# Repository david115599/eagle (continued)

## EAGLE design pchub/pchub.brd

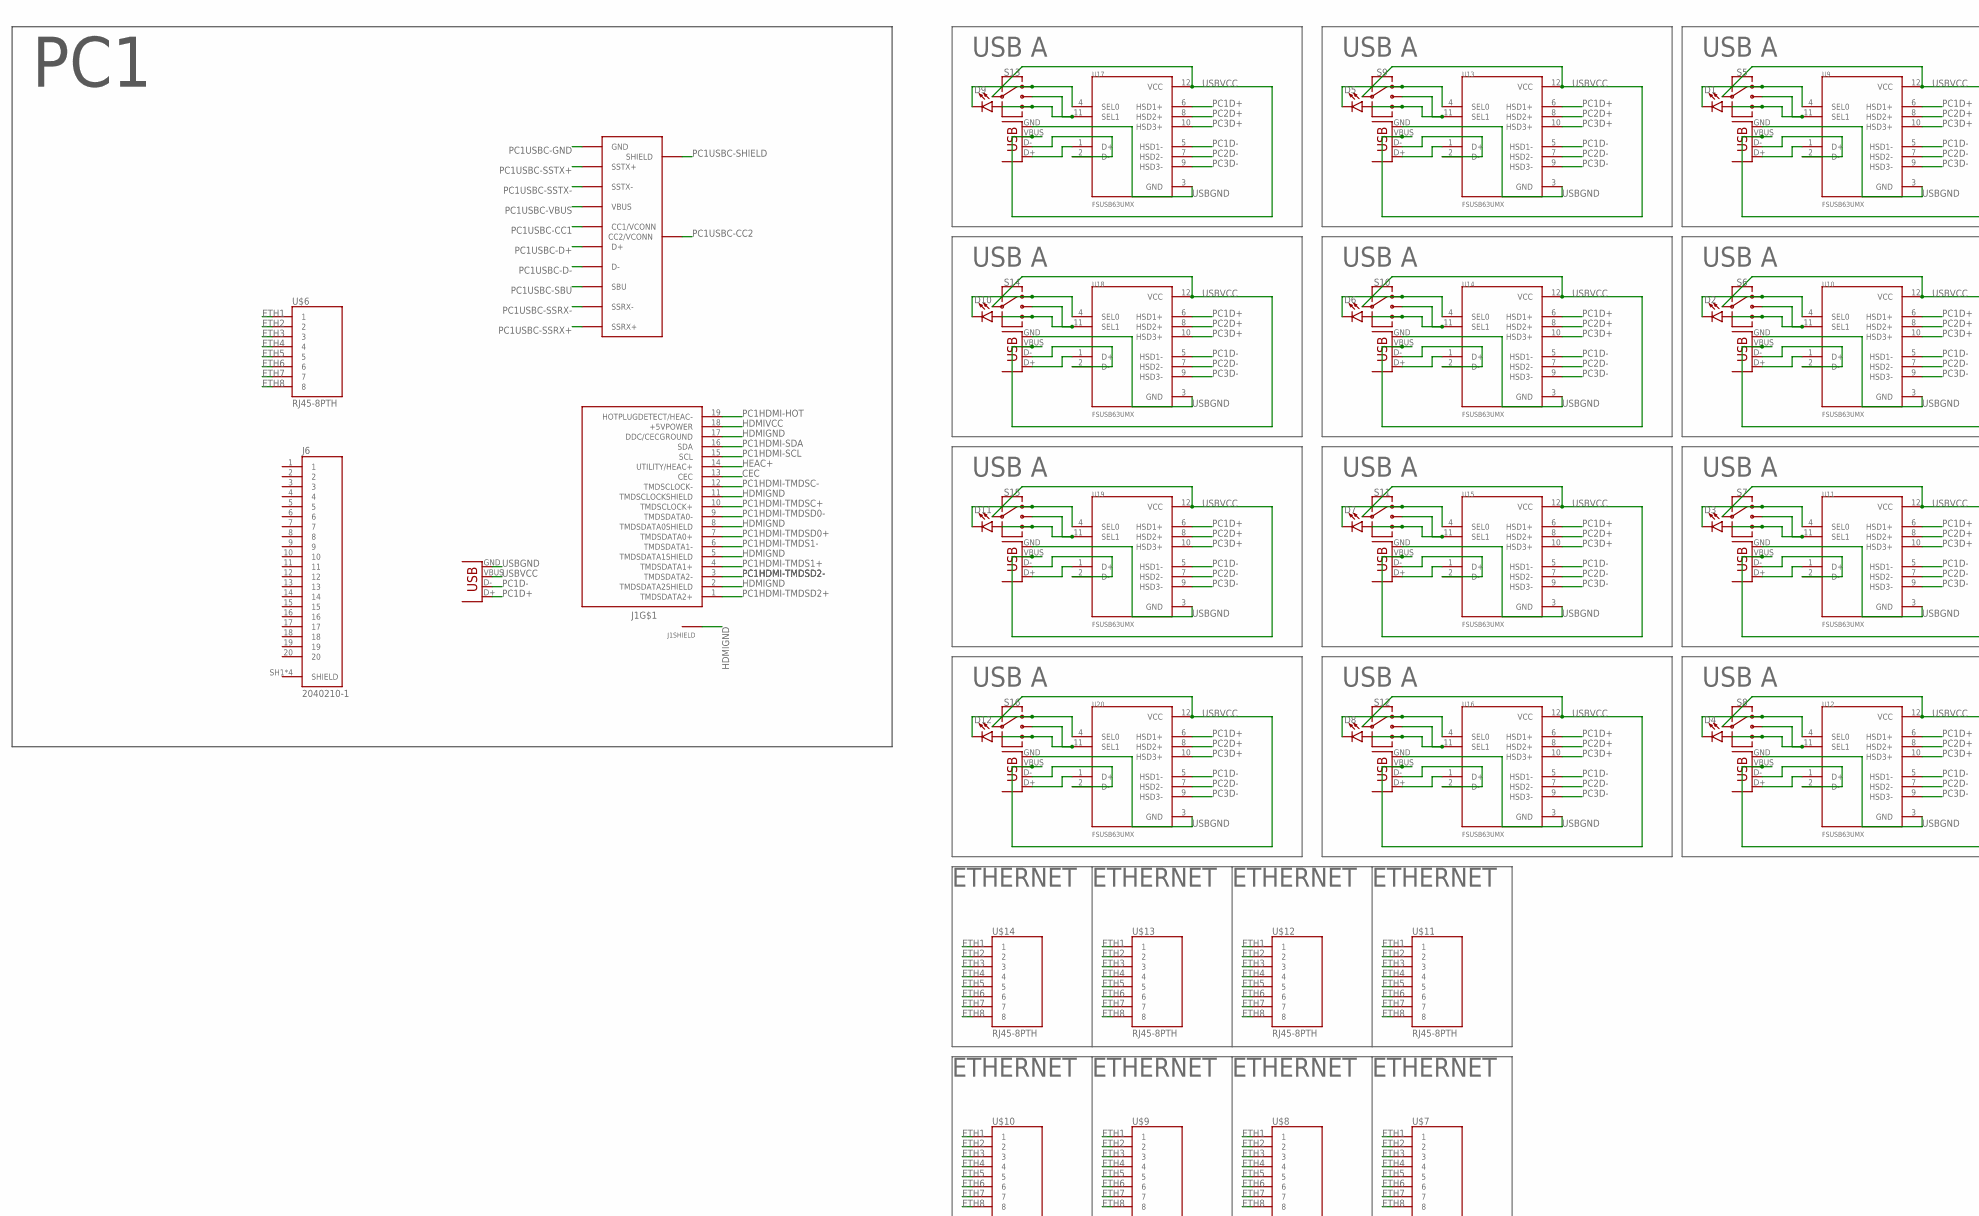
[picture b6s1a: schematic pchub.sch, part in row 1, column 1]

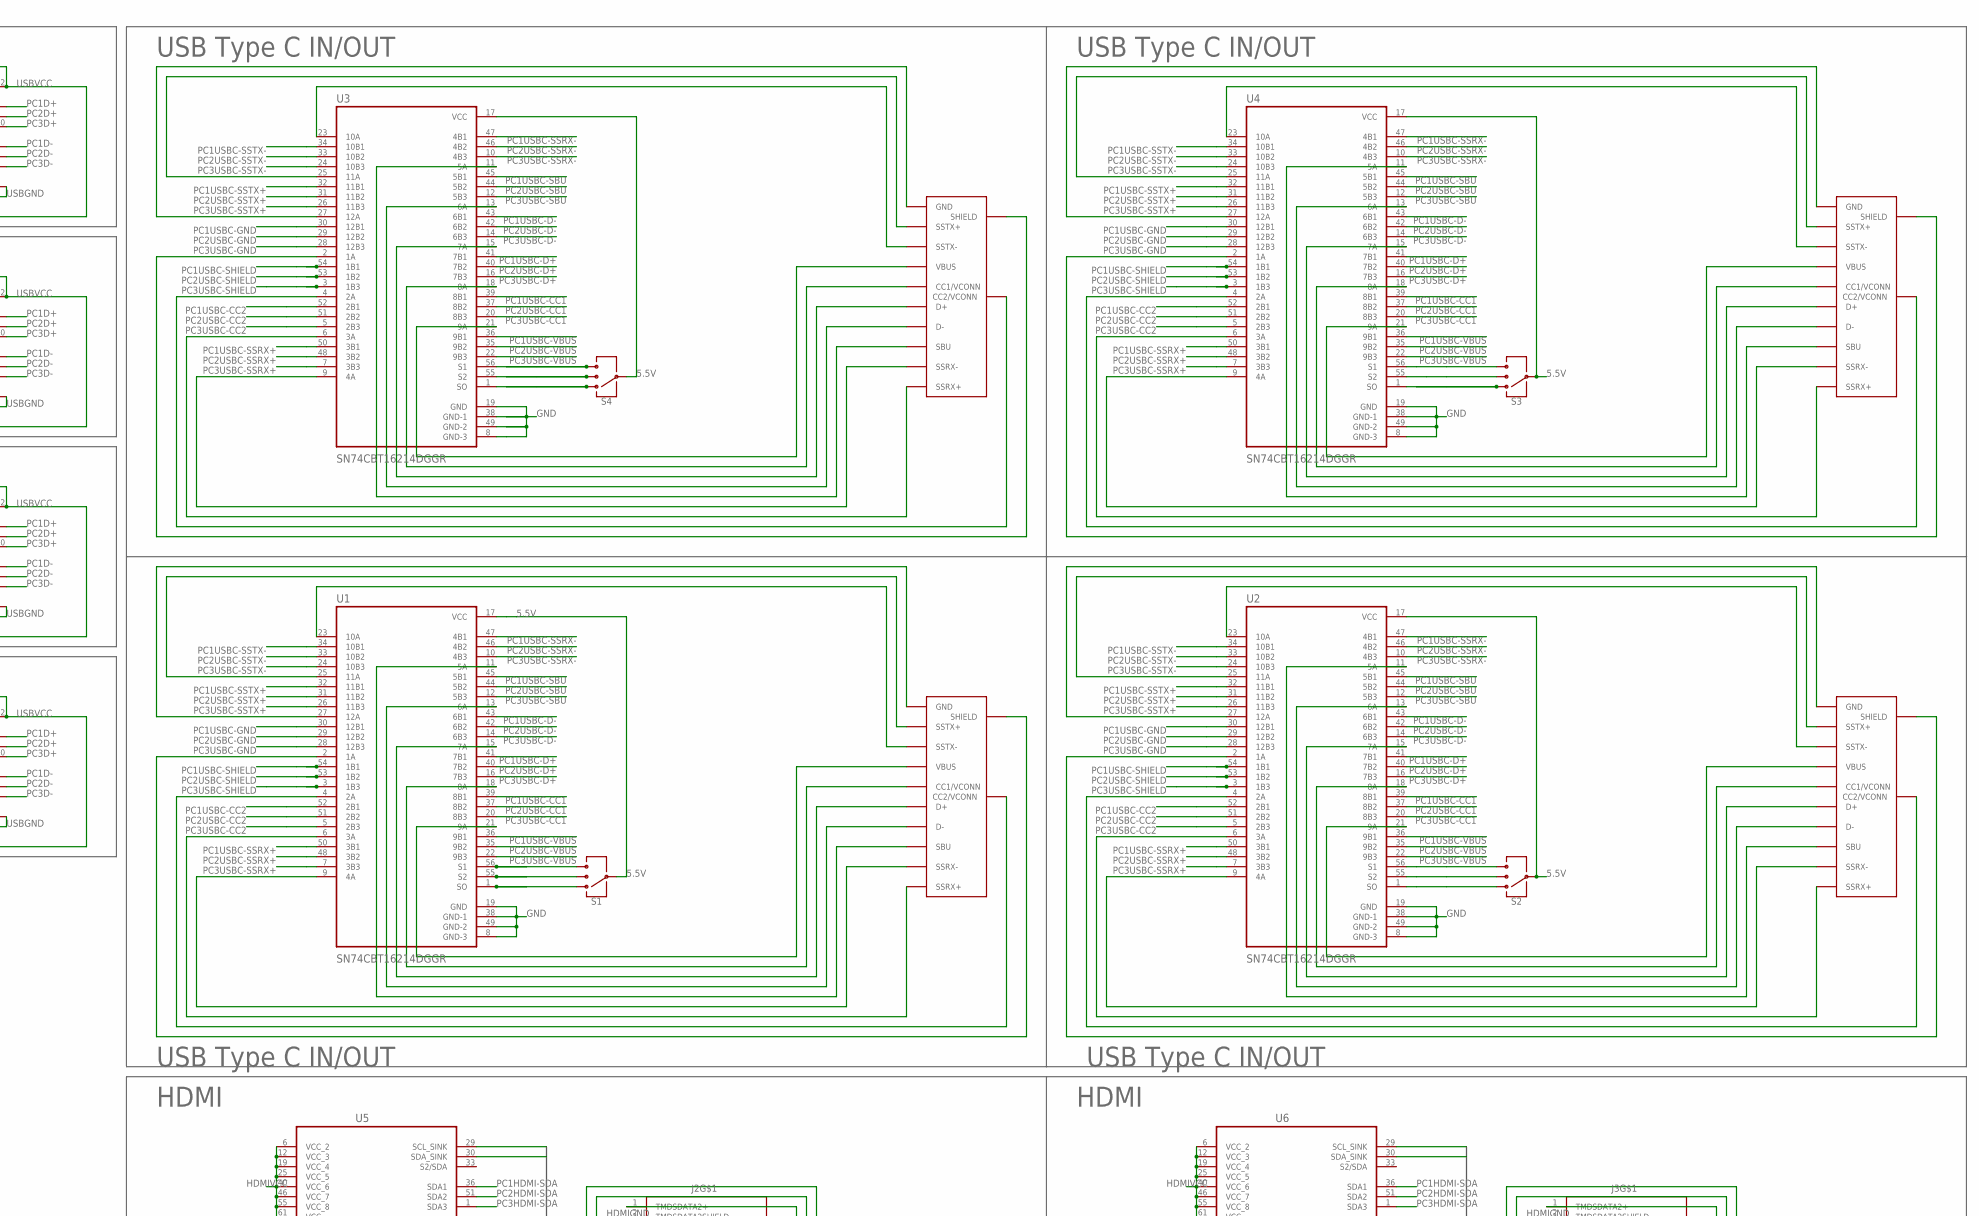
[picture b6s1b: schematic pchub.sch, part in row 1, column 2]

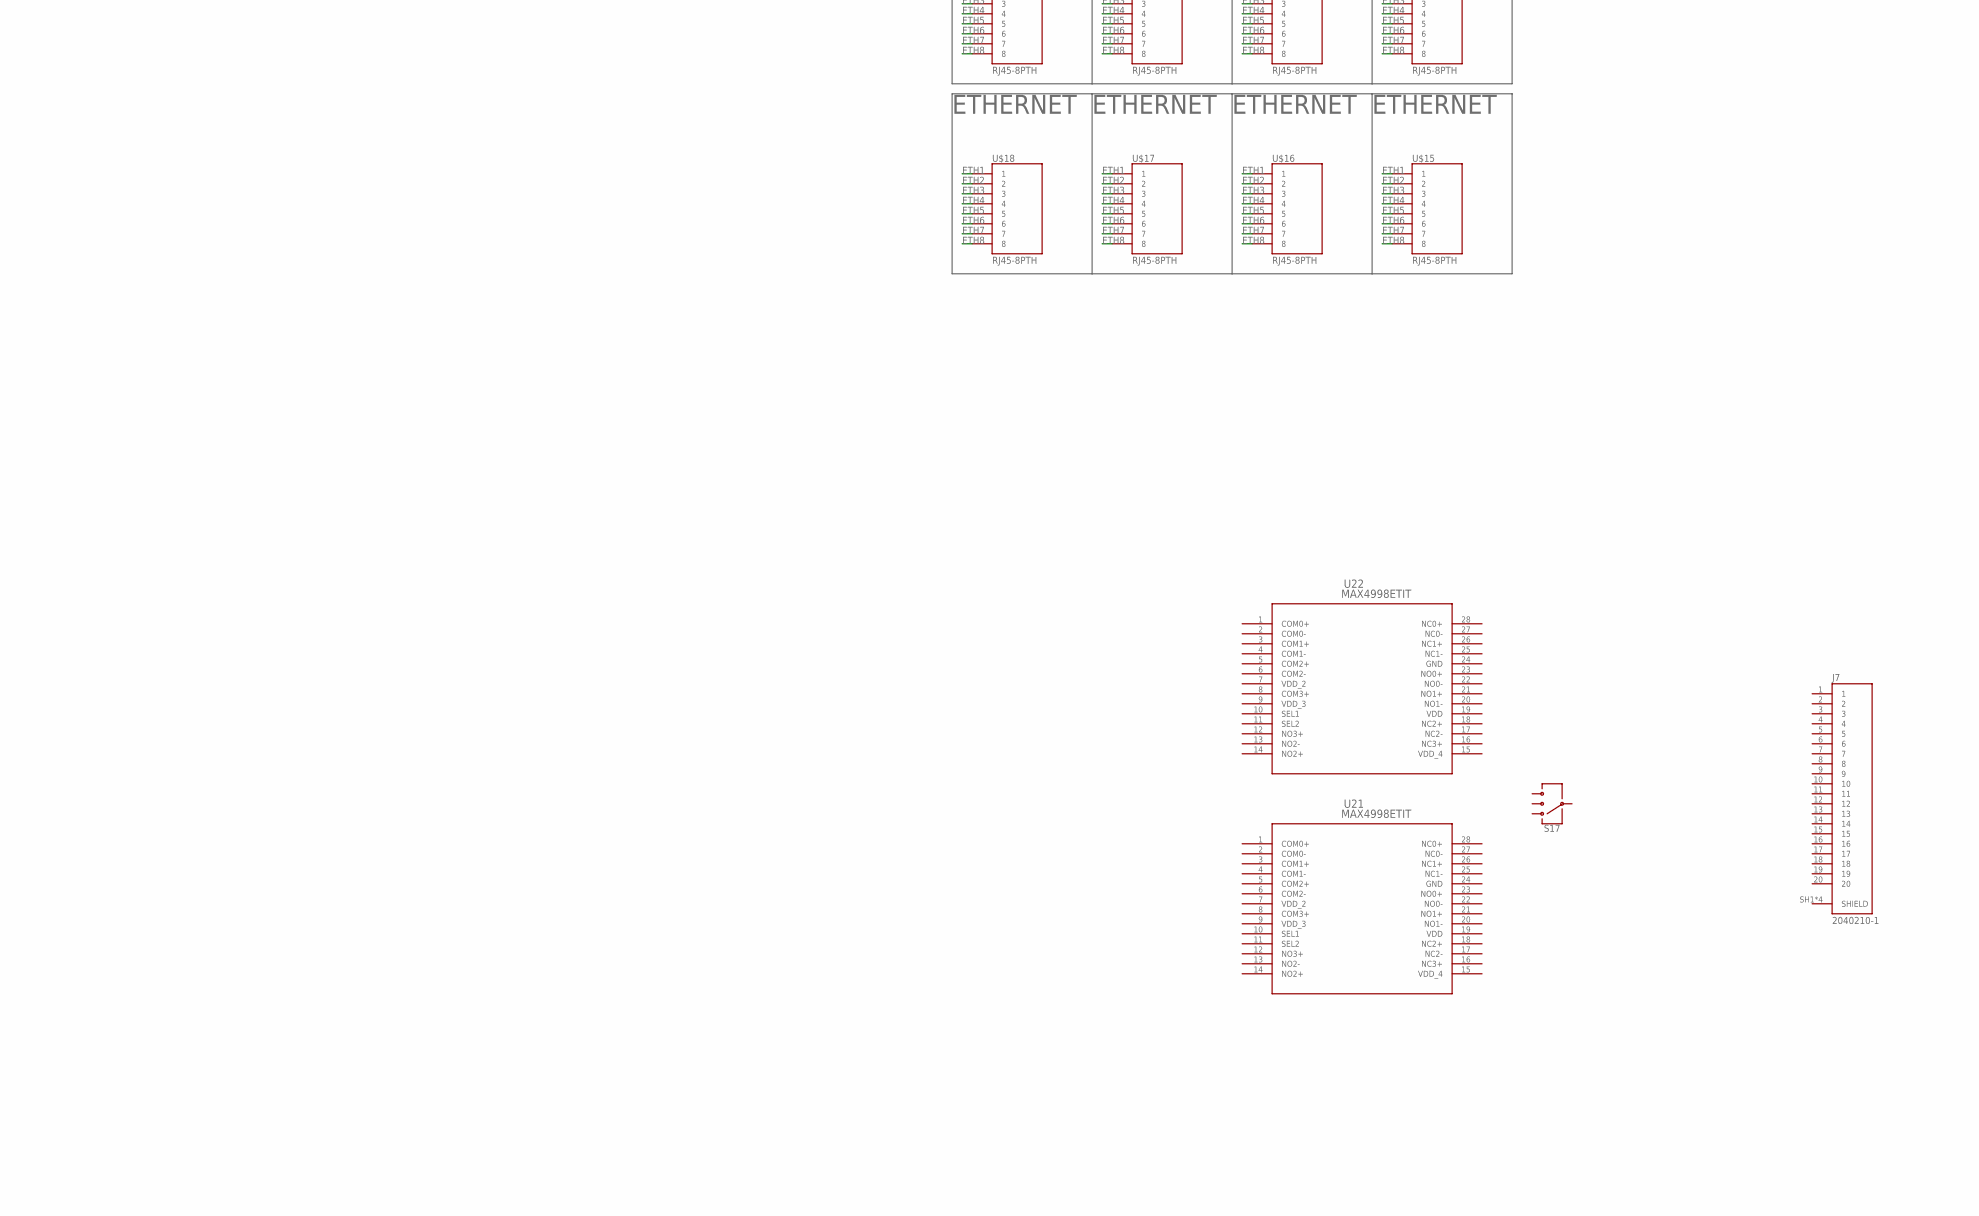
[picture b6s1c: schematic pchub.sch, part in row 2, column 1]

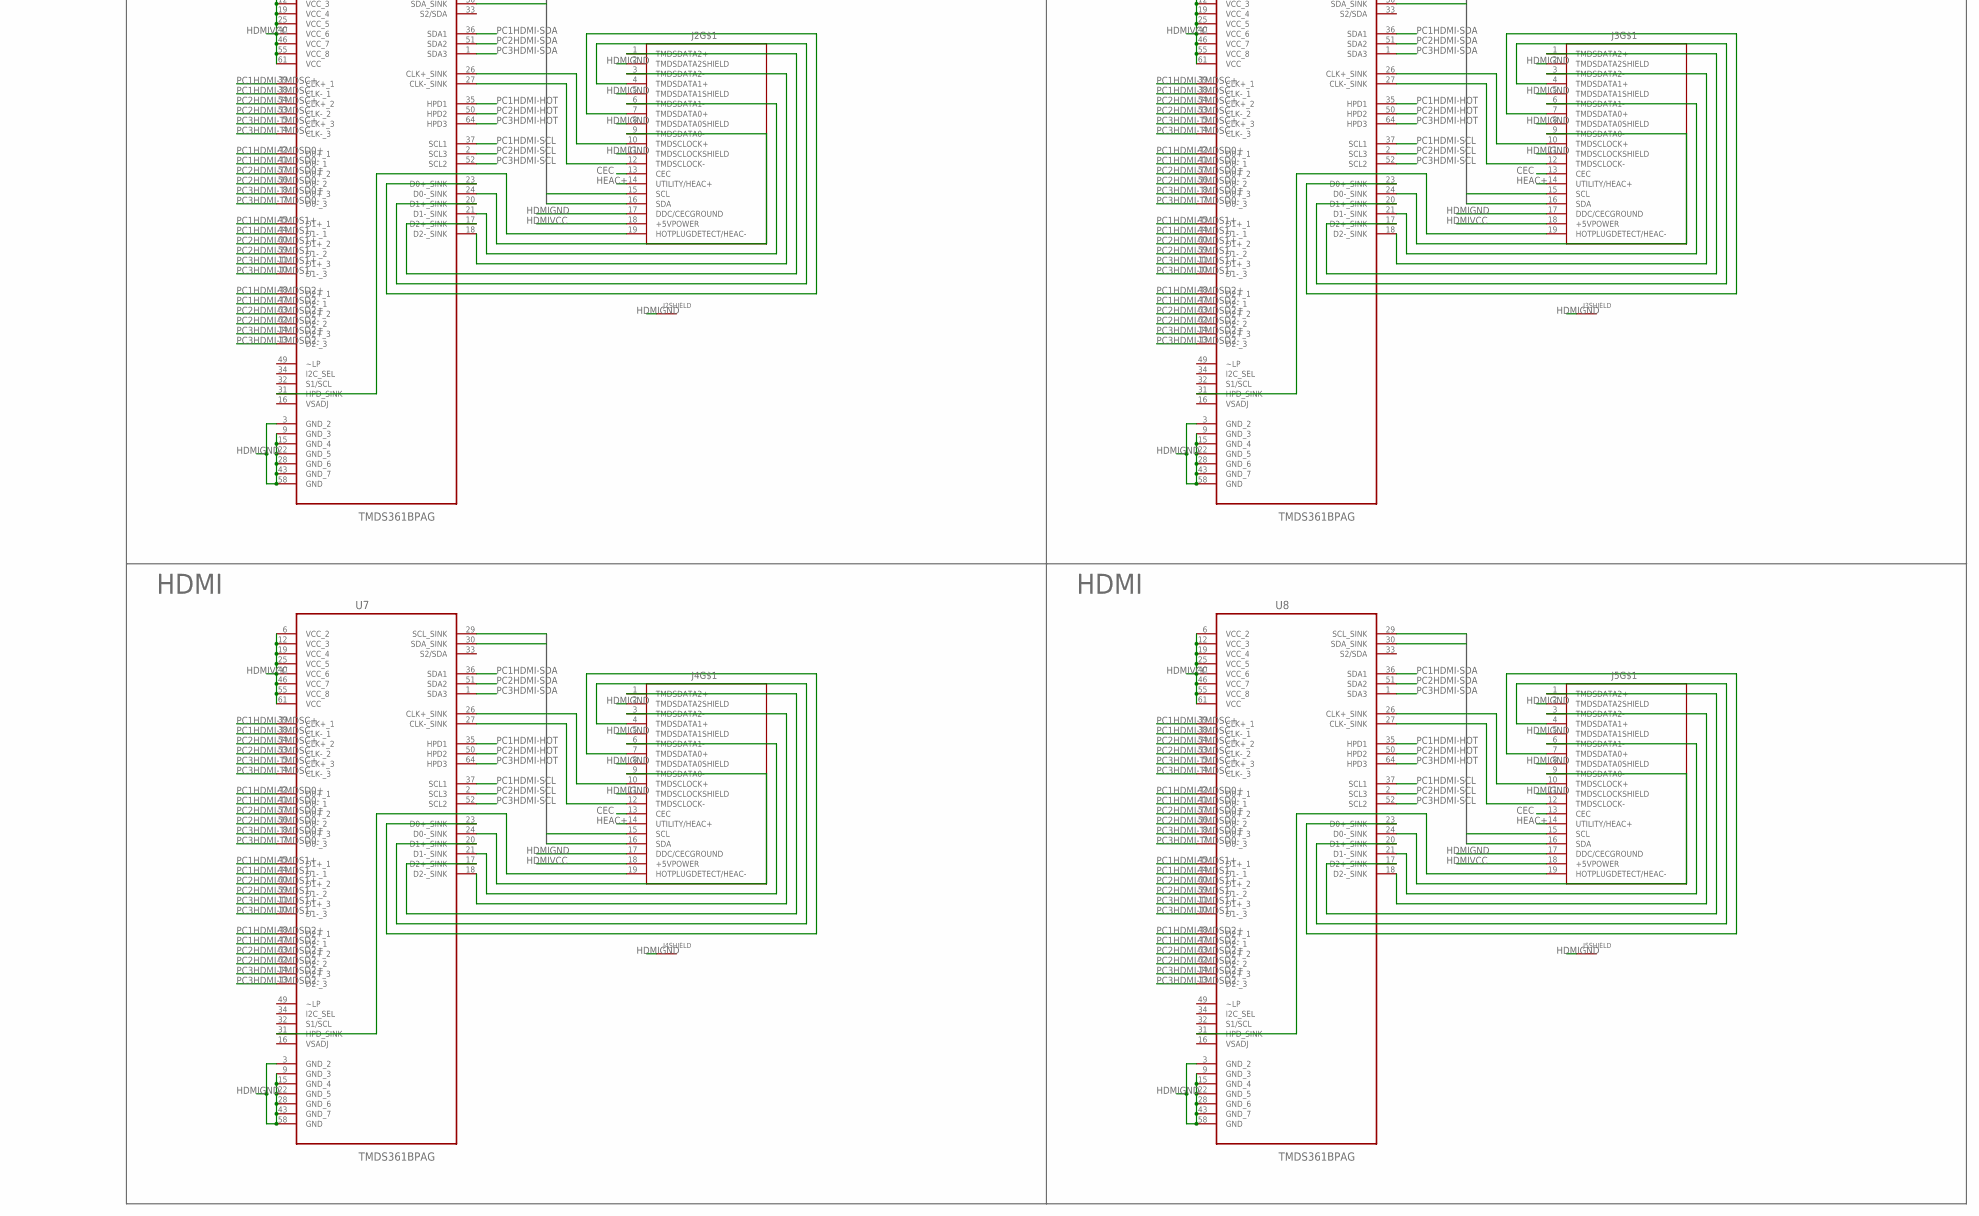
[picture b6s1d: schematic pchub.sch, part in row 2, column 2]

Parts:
D1, D2, D3, D4, D5, D6, D7, D8, D9, D10, D11, D12: LED-FKIT-1206; FKIT-LED-1206
J1, J2, J3, J4, J5: 685119134923
J6, J7: 2040210-1; TE_2040210-1
S1, S2, S3, S4, S5, S6, S7, S8, S9, S10, S11, S12, S13, S14, S15, S16, S17: SWITCH-SP3T-SMD; SWITCH_SP3T_SMD
U1, U2, U3, U4: SN74CBT16214DGGR; SOP50P810X120-56N
U5, U6, U7, U8: TMDS361BPAG; QFP50P1200X1200X120-64N
U9, U10, U11, U12, U13, U14, U15, U16, U17, U18, U19, U20: FSUSB63UMX; QFN40P180X180X55-12N
U21, U22: MAX4998ETIT; 21-0184D
U$1, U$2, U$3, U$4, U$5: USB-TYPE-C; USB-TYPE-C-SMT
U$6, U$7, U$8, U$9, U$10, U$11, U$12, U$13, U$14, U$15, U$16, U$17, U$18: RJ45-8PTH; RJ45-8
X1, X2, X3, X4, X5, X6, X7, X8, X9, X10, X11, X12, X13: USB; USB-A-S-NOSILK-FEMALE

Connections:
5.5V: S1.3, S2.3, S3.3, S4.3, U1.17 (VCC), U2.17 (VCC), U3.17 (VCC), U4.17 (VCC)
CEC: J1.13 (CEC), J2.13 (CEC), J3.13 (CEC), J4.13 (CEC), J5.13 (CEC)
ETH1: U$6.1, U$7.1, U$8.1, U$9.1, U$10.1, U$11.1, U$12.1, U$13.1, U$14.1, U$15.1, U$16.1, U$17.1, U$18.1
ETH2: U$6.2, U$7.2, U$8.2, U$9.2, U$10.2, U$11.2, U$12.2, U$13.2, U$14.2, U$15.2, U$16.2, U$17.2, U$18.2
ETH3: U$6.3, U$7.3, U$8.3, U$9.3, U$10.3, U$11.3, U$12.3, U$13.3, U$14.3, U$15.3, U$16.3, U$17.3, U$18.3
ETH4: U$6.4, U$7.4, U$8.4, U$9.4, U$10.4, U$11.4, U$12.4, U$13.4, U$14.4, U$15.4, U$16.4, U$17.4, U$18.4
ETH5: U$6.5, U$7.5, U$8.5, U$9.5, U$10.5, U$11.5, U$12.5, U$13.5, U$14.5, U$15.5, U$16.5, U$17.5, U$18.5
ETH6: U$6.6, U$7.6, U$8.6, U$9.6, U$10.6, U$11.6, U$12.6, U$13.6, U$14.6, U$15.6, U$16.6, U$17.6, U$18.6
ETH7: U$6.7, U$7.7, U$8.7, U$9.7, U$10.7, U$11.7, U$12.7, U$13.7, U$14.7, U$15.7, U$16.7, U$17.7, U$18.7
ETH8: U$6.8, U$7.8, U$8.8, U$9.8, U$10.8, U$11.8, U$12.8, U$13.8, U$14.8, U$15.8, U$16.8, U$17.8, U$18.8
GND: U1.8 (GND-3), U1.19 (GND), U1.38 (GND-1), U1.49 (GND-2), U2.8 (GND-3), U2.19 (GND), U2.38 (GND-1), U2.49 (GND-2), U3.8 (GND-3), U3.19 (GND), U3.38 (GND-1), U3.49 (GND-2), U4.8 (GND-3), U4.19 (GND), U4.38 (GND-1), U4.49 (GND-2), U21.24 (GND), U22.24 (GND)
HDMIGND: J1.2 (TMDSDATA2SHIELD), J1.5 (TMDSDATA1SHIELD), J1.8 (TMDSDATA0SHIELD), J1.11 (TMDSCLOCKSHIELD), J1.17 (DDC/CECGROUND), J1.SHELL (SHIELD), J1.SHELL1 (SHIELD), J1.SHELL2 (SHIELD), J1.SHELL3 (SHIELD), J2.2 (TMDSDATA2SHIELD), J2.5 (TMDSDATA1SHIELD), J2.8 (TMDSDATA0SHIELD), J2.11 (TMDSCLOCKSHIELD), J2.17 (DDC/CECGROUND), J2.SHELL (SHIELD), J2.SHELL1 (SHIELD), J2.SHELL2 (SHIELD), J2.SHELL3 (SHIELD), J3.2 (TMDSDATA2SHIELD), J3.5 (TMDSDATA1SHIELD), J3.8 (TMDSDATA0SHIELD), J3.11 (TMDSCLOCKSHIELD), J3.17 (DDC/CECGROUND), J3.SHELL (SHIELD), J3.SHELL1 (SHIELD), J3.SHELL2 (SHIELD), J3.SHELL3 (SHIELD), J4.2 (TMDSDATA2SHIELD), J4.5 (TMDSDATA1SHIELD), J4.8 (TMDSDATA0SHIELD), J4.11 (TMDSCLOCKSHIELD), J4.17 (DDC/CECGROUND), J4.SHELL (SHIELD), J4.SHELL1 (SHIELD), J4.SHELL2 (SHIELD), J4.SHELL3 (SHIELD), J5.2 (TMDSDATA2SHIELD), J5.5 (TMDSDATA1SHIELD), J5.8 (TMDSDATA0SHIELD), J5.11 (TMDSCLOCKSHIELD), J5.17 (DDC/CECGROUND), J5.SHELL (SHIELD), J5.SHELL1 (SHIELD), J5.SHELL2 (SHIELD), J5.SHELL3 (SHIELD), U5.3 (GND_2), U5.9 (GND_3), U5.15 (GND_4), U5.22 (GND_5), U5.28 (GND_6), U5.43 (GND_7), U5.58 (GND), U6.3 (GND_2), U6.9 (GND_3), U6.15 (GND_4), U6.22 (GND_5), U6.28 (GND_6), U6.43 (GND_7), U6.58 (GND), U7.3 (GND_2), U7.9 (GND_3), U7.15 (GND_4), U7.22 (GND_5), U7.28 (GND_6), U7.43 (GND_7), U7.58 (GND), U8.3 (GND_2), U8.9 (GND_3), U8.15 (GND_4), U8.22 (GND_5), U8.28 (GND_6), U8.43 (GND_7), U8.58 (GND)
HDMIVCC: J1.18 (+5VPOWER), J2.18 (+5VPOWER), J3.18 (+5VPOWER), J4.18 (+5VPOWER), J5.18 (+5VPOWER), U5.6 (VCC_2), U5.12 (VCC_3), U5.19 (VCC_4), U5.25 (VCC_5), U5.40 (VCC_6), U5.46 (VCC_7), U5.55 (VCC_8), U5.61 (VCC), U6.6 (VCC_2), U6.12 (VCC_3), U6.19 (VCC_4), U6.25 (VCC_5), U6.40 (VCC_6), U6.46 (VCC_7), U6.55 (VCC_8), U6.61 (VCC), U7.6 (VCC_2), U7.12 (VCC_3), U7.19 (VCC_4), U7.25 (VCC_5), U7.40 (VCC_6), U7.46 (VCC_7), U7.55 (VCC_8), U7.61 (VCC), U8.6 (VCC_2), U8.12 (VCC_3), U8.19 (VCC_4), U8.25 (VCC_5), U8.40 (VCC_6), U8.46 (VCC_7), U8.55 (VCC_8), U8.61 (VCC)
HEAC+: J1.14 (UTILITY/HEAC+), J2.14 (UTILITY/HEAC+), J3.14 (UTILITY/HEAC+), J4.14 (UTILITY/HEAC+), J5.14 (UTILITY/HEAC+)
unnamed: U2.18 (8A), U$2.5 (CC1/VCONN)
unnamed: U2.23 (10A), U$2.3 (SSTX-), U$2.B3 (SSTX-)
unnamed: U2.25 (11A), U$2.2 (SSTX+), U$2.B2 (SSTX+)
unnamed: U2.27 (12A), U$2.1 (GND), U$2.12 (GND), U$2.B1 (GND), U$2.B12 (GND)
unnamed: U2.2 (1A), U$2.P$1 (SHIELD), U$2.P$2 (SHIELD), U$2.P$3 (SHIELD), U$2.P$4 (SHIELD), U$2.P$5 (SHIELD), U$2.P$6 (SHIELD), U$2.P$7 (SHIELD), U$2.P$8 (SHIELD), U$2.P$9 (SHIELD), U$2.P$10 (SHIELD), U$2.P$11 (SHIELD), U$2.P$12 (SHIELD), U$2.P$13 (SHIELD), U$2.P$14 (SHIELD), U$2.P$15 (SHIELD), U$2.P$16 (SHIELD), U$2.P$17 (SHIELD), U$2.P$18 (SHIELD), U$2.P$19 (SHIELD), U$2.P$20 (SHIELD), U$2.P$21 (SHIELD), U$2.P$22 (SHIELD), U$2.P$23 (SHIELD), U$2.P$24 (SHIELD), U$2.P$25 (SHIELD), U$2.P$26 (SHIELD), U$2.P$27 (SHIELD), U$2.P$28 (SHIELD)
unnamed: U2.4 (2A), U$2.B5 (CC2/VCONN)
unnamed: U2.15 (7A), U$2.6 (D+), U$2.B6 (D+)
unnamed: U2.13 (6A), U$2.7 (D-), U$2.B7 (D-)
unnamed: U2.11 (5A), U$2.8 (SBU), U$2.B8 (SBU)
unnamed: U2.9 (4A), U$2.10 (SSRX-), U$2.B10 (SSRX-)
unnamed: U2.6 (3A), U$2.11 (SSRX+), U$2.B11 (SSRX+)
unnamed: U3.18 (8A), U$4.5 (CC1/VCONN)
unnamed: U3.23 (10A), U$4.3 (SSTX-), U$4.B3 (SSTX-)
unnamed: U3.25 (11A), U$4.2 (SSTX+), U$4.B2 (SSTX+)
unnamed: U3.27 (12A), U$4.1 (GND), U$4.12 (GND), U$4.B1 (GND), U$4.B12 (GND)
unnamed: U3.2 (1A), U$4.P$1 (SHIELD), U$4.P$2 (SHIELD), U$4.P$3 (SHIELD), U$4.P$4 (SHIELD), U$4.P$5 (SHIELD), U$4.P$6 (SHIELD), U$4.P$7 (SHIELD), U$4.P$8 (SHIELD), U$4.P$9 (SHIELD), U$4.P$10 (SHIELD), U$4.P$11 (SHIELD), U$4.P$12 (SHIELD), U$4.P$13 (SHIELD), U$4.P$14 (SHIELD), U$4.P$15 (SHIELD), U$4.P$16 (SHIELD), U$4.P$17 (SHIELD), U$4.P$18 (SHIELD), U$4.P$19 (SHIELD), U$4.P$20 (SHIELD), U$4.P$21 (SHIELD), U$4.P$22 (SHIELD), U$4.P$23 (SHIELD), U$4.P$24 (SHIELD), U$4.P$25 (SHIELD), U$4.P$26 (SHIELD), U$4.P$27 (SHIELD), U$4.P$28 (SHIELD)
unnamed: U3.4 (2A), U$4.B5 (CC2/VCONN)
unnamed: U3.15 (7A), U$4.6 (D+), U$4.B6 (D+)
unnamed: U3.13 (6A), U$4.7 (D-), U$4.B7 (D-)
unnamed: U3.11 (5A), U$4.8 (SBU), U$4.B8 (SBU)
unnamed: U3.9 (4A), U$4.10 (SSRX-), U$4.B10 (SSRX-)
unnamed: U3.6 (3A), U$4.11 (SSRX+), U$4.B11 (SSRX+)
unnamed: U4.18 (8A), U$5.5 (CC1/VCONN)
unnamed: U4.23 (10A), U$5.3 (SSTX-), U$5.B3 (SSTX-)
unnamed: U4.25 (11A), U$5.2 (SSTX+), U$5.B2 (SSTX+)
unnamed: U4.27 (12A), U$5.1 (GND), U$5.12 (GND), U$5.B1 (GND), U$5.B12 (GND)
unnamed: U4.2 (1A), U$5.P$1 (SHIELD), U$5.P$2 (SHIELD), U$5.P$3 (SHIELD), U$5.P$4 (SHIELD), U$5.P$5 (SHIELD), U$5.P$6 (SHIELD), U$5.P$7 (SHIELD), U$5.P$8 (SHIELD), U$5.P$9 (SHIELD), U$5.P$10 (SHIELD), U$5.P$11 (SHIELD), U$5.P$12 (SHIELD), U$5.P$13 (SHIELD), U$5.P$14 (SHIELD), U$5.P$15 (SHIELD), U$5.P$16 (SHIELD), U$5.P$17 (SHIELD), U$5.P$18 (SHIELD), U$5.P$19 (SHIELD), U$5.P$20 (SHIELD), U$5.P$21 (SHIELD), U$5.P$22 (SHIELD), U$5.P$23 (SHIELD), U$5.P$24 (SHIELD), U$5.P$25 (SHIELD), U$5.P$26 (SHIELD), U$5.P$27 (SHIELD), U$5.P$28 (SHIELD)
unnamed: U4.4 (2A), U$5.B5 (CC2/VCONN)
unnamed: U4.15 (7A), U$5.6 (D+), U$5.B6 (D+)
unnamed: U4.13 (6A), U$5.7 (D-), U$5.B7 (D-)
unnamed: U4.11 (5A), U$5.8 (SBU), U$5.B8 (SBU)
unnamed: U4.9 (4A), U$5.10 (SSRX-), U$5.B10 (SSRX-)
unnamed: U4.6 (3A), U$5.11 (SSRX+), U$5.B11 (SSRX+)
unnamed: S2.4, U2.56 (S1)
unnamed: S1.4, U1.56 (S1)
unnamed: S1.2, U1.55 (S2)
unnamed: S1.1, U1.1 (SO)
unnamed: S2.2, U2.55 (S2)
unnamed: S2.1, U2.1 (SO)
unnamed: S3.4, U4.56 (S1)
unnamed: S3.2, U4.55 (S2)
unnamed: S3.1, U4.1 (SO)
unnamed: S4.4, U3.56 (S1)
unnamed: S4.2, U3.55 (S2)
unnamed: S4.1, U3.1 (SO)
unnamed: J2.3 (TMDSDATA2-), U5.18 (D2-_SINK)
unnamed: J2.1 (TMDSDATA2+), U5.17 (D2+_SINK)
unnamed: J2.6 (TMDSDATA1-), U5.21 (D1-_SINK)
unnamed: J2.4 (TMDSDATA1+), U5.20 (D1+_SINK)
unnamed: J2.9 (TMDSDATA0-), U5.24 (D0-_SINK)
unnamed: J2.7 (TMDSDATA0+), U5.23 (D0+_SINK)
unnamed: J2.12 (TMDSCLOCK-), U5.27 (CLK-_SINK)
unnamed: J2.10 (TMDSCLOCK+), U5.26 (CLK+_SINK)
unnamed: J2.19 (HOTPLUGDETECT/HEAC-), U5.31 (HPD_SINK)
unnamed: J3.3 (TMDSDATA2-), U6.18 (D2-_SINK)
unnamed: J3.1 (TMDSDATA2+), U6.17 (D2+_SINK)
unnamed: J3.6 (TMDSDATA1-), U6.21 (D1-_SINK)
unnamed: J3.4 (TMDSDATA1+), U6.20 (D1+_SINK)
unnamed: J3.9 (TMDSDATA0-), U6.24 (D0-_SINK)
unnamed: J3.7 (TMDSDATA0+), U6.23 (D0+_SINK)
unnamed: J3.12 (TMDSCLOCK-), U6.27 (CLK-_SINK)
unnamed: J3.10 (TMDSCLOCK+), U6.26 (CLK+_SINK)
unnamed: J3.19 (HOTPLUGDETECT/HEAC-), U6.31 (HPD_SINK)
unnamed: J4.3 (TMDSDATA2-), U7.18 (D2-_SINK)
unnamed: J4.1 (TMDSDATA2+), U7.17 (D2+_SINK)
unnamed: J4.6 (TMDSDATA1-), U7.21 (D1-_SINK)
unnamed: J4.4 (TMDSDATA1+), U7.20 (D1+_SINK)
unnamed: J4.9 (TMDSDATA0-), U7.24 (D0-_SINK)
unnamed: J4.7 (TMDSDATA0+), U7.23 (D0+_SINK)
unnamed: J4.12 (TMDSCLOCK-), U7.27 (CLK-_SINK)
unnamed: J4.10 (TMDSCLOCK+), U7.26 (CLK+_SINK)
unnamed: J4.19 (HOTPLUGDETECT/HEAC-), U7.31 (HPD_SINK)
unnamed: J5.3 (TMDSDATA2-), U8.18 (D2-_SINK)
unnamed: J5.1 (TMDSDATA2+), U8.17 (D2+_SINK)
unnamed: J5.6 (TMDSDATA1-), U8.21 (D1-_SINK)
unnamed: J5.4 (TMDSDATA1+), U8.20 (D1+_SINK)
unnamed: J5.9 (TMDSDATA0-), U8.24 (D0-_SINK)
unnamed: J5.7 (TMDSDATA0+), U8.23 (D0+_SINK)
unnamed: J5.12 (TMDSCLOCK-), U8.27 (CLK-_SINK)
unnamed: J5.10 (TMDSCLOCK+), U8.26 (CLK+_SINK)
unnamed: J5.19 (HOTPLUGDETECT/HEAC-), U8.31 (HPD_SINK)
unnamed: U9.2 (D-), X1.D-
unnamed: U9.1 (D+), X1.D+
unnamed: D1.C, S5.1, U9.4 (SEL0)
unnamed: U10.2 (D-), X3.D-
unnamed: U10.1 (D+), X3.D+
unnamed: D1.A, S5.2, S5.4, U9.11 (SEL1)
unnamed: D2.C, S6.1, U10.4 (SEL0)
unnamed: D2.A, S6.2, S6.4, U10.11 (SEL1)
unnamed: U11.2 (D-), X4.D-
unnamed: U11.1 (D+), X4.D+
unnamed: D3.C, S7.1, U11.4 (SEL0)
unnamed: D3.A, S7.2, S7.4, U11.11 (SEL1)
unnamed: U12.2 (D-), X5.D-
unnamed: U12.1 (D+), X5.D+
unnamed: D4.C, S8.1, U12.4 (SEL0)
unnamed: D4.A, S8.2, S8.4, U12.11 (SEL1)
unnamed: U13.2 (D-), X6.D-
unnamed: U13.1 (D+), X6.D+
unnamed: D5.C, S9.1, U13.4 (SEL0)
unnamed: D5.A, S9.2, S9.4, U13.11 (SEL1)
unnamed: U14.2 (D-), X7.D-
unnamed: U14.1 (D+), X7.D+
unnamed: D6.C, S10.1, U14.4 (SEL0)
unnamed: D6.A, S10.2, S10.4, U14.11 (SEL1)
unnamed: U15.2 (D-), X8.D-
unnamed: U15.1 (D+), X8.D+
unnamed: D7.C, S11.1, U15.4 (SEL0)
unnamed: D7.A, S11.2, S11.4, U15.11 (SEL1)
unnamed: U16.2 (D-), X9.D-
unnamed: U16.1 (D+), X9.D+
unnamed: D8.C, S12.1, U16.4 (SEL0)
unnamed: D8.A, S12.2, S12.4, U16.11 (SEL1)
unnamed: U17.2 (D-), X10.D-
unnamed: U17.1 (D+), X10.D+
unnamed: D9.C, S13.1, U17.4 (SEL0)
unnamed: D9.A, S13.2, S13.4, U17.11 (SEL1)
unnamed: U18.2 (D-), X11.D-
unnamed: U18.1 (D+), X11.D+
unnamed: D10.C, S14.1, U18.4 (SEL0)
unnamed: D10.A, S14.2, S14.4, U18.11 (SEL1)
unnamed: U19.2 (D-), X12.D-
unnamed: U19.1 (D+), X12.D+
unnamed: D11.C, S15.1, U19.4 (SEL0)
unnamed: D11.A, S15.2, S15.4, U19.11 (SEL1)
unnamed: U20.2 (D-), X13.D-
unnamed: U20.1 (D+), X13.D+
unnamed: D12.C, S16.1, U20.4 (SEL0)
unnamed: D12.A, S16.2, S16.4, U20.11 (SEL1)
unnamed: J7.1, U22.1 (COM0+)
unnamed: J7.3, U22.2 (COM0-)
unnamed: U1.18 (8A), U$3.5 (CC1/VCONN)
unnamed: U1.23 (10A), U$3.3 (SSTX-), U$3.B3 (SSTX-)
unnamed: U1.25 (11A), U$3.2 (SSTX+), U$3.B2 (SSTX+)
unnamed: U1.27 (12A), U$3.1 (GND), U$3.12 (GND), U$3.B1 (GND), U$3.B12 (GND)
unnamed: U1.2 (1A), U$3.P$1 (SHIELD), U$3.P$2 (SHIELD), U$3.P$3 (SHIELD), U$3.P$4 (SHIELD), U$3.P$5 (SHIELD), U$3.P$6 (SHIELD), U$3.P$7 (SHIELD), U$3.P$8 (SHIELD), U$3.P$9 (SHIELD), U$3.P$10 (SHIELD), U$3.P$11 (SHIELD), U$3.P$12 (SHIELD), U$3.P$13 (SHIELD), U$3.P$14 (SHIELD), U$3.P$15 (SHIELD), U$3.P$16 (SHIELD), U$3.P$17 (SHIELD), U$3.P$18 (SHIELD), U$3.P$19 (SHIELD), U$3.P$20 (SHIELD), U$3.P$21 (SHIELD), U$3.P$22 (SHIELD), U$3.P$23 (SHIELD), U$3.P$24 (SHIELD), U$3.P$25 (SHIELD), U$3.P$26 (SHIELD), U$3.P$27 (SHIELD), U$3.P$28 (SHIELD)
unnamed: U1.4 (2A), U$3.B5 (CC2/VCONN)
unnamed: U1.15 (7A), U$3.6 (D+), U$3.B6 (D+)
unnamed: U1.13 (6A), U$3.7 (D-), U$3.B7 (D-)
unnamed: U1.11 (5A), U$3.8 (SBU), U$3.B8 (SBU)
unnamed: U1.9 (4A), U$3.10 (SSRX-), U$3.B10 (SSRX-)
unnamed: U1.6 (3A), U$3.11 (SSRX+), U$3.B11 (SSRX+)
PC1D+: U9.6 (HSD1+), U10.6 (HSD1+), U11.6 (HSD1+), U12.6 (HSD1+), U13.6 (HSD1+), U14.6 (HSD1+), U15.6 (HSD1+), U16.6 (HSD1+), U17.6 (HSD1+), U18.6 (HSD1+), U19.6 (HSD1+), U20.6 (HSD1+), X2.D+
PC1D-: U9.5 (HSD1-), U10.5 (HSD1-), U11.5 (HSD1-), U12.5 (HSD1-), U13.5 (HSD1-), U14.5 (HSD1-), U15.5 (HSD1-), U16.5 (HSD1-), U17.5 (HSD1-), U18.5 (HSD1-), U19.5 (HSD1-), U20.5 (HSD1-), X2.D-
PC1HDMI-HOT: J1.19 (HOTPLUGDETECT/HEAC-), U5.35 (HPD1), U6.35 (HPD1), U7.35 (HPD1), U8.35 (HPD1)
PC1HDMI-SCL: J1.15 (SCL), U5.37 (SCL1), U6.37 (SCL1), U7.37 (SCL1), U8.37 (SCL1)
PC1HDMI-SDA: J1.16 (SDA), U5.36 (SDA1), U6.36 (SDA1), U7.36 (SDA1), U8.36 (SDA1)
PC1HDMI-TMDS1+: J1.4 (TMDSDATA1+), U5.45 (D1+_1), U6.45 (D1+_1), U7.45 (D1+_1), U8.45 (D1+_1)
PC1HDMI-TMDS1-: J1.6 (TMDSDATA1-), U5.44 (D1-_1), U6.44 (D1-_1), U7.44 (D1-_1), U8.44 (D1-_1)
PC1HDMI-TMDSC+: J1.10 (TMDSCLOCK+), U5.39 (CLK+_1), U6.39 (CLK+_1), U7.39 (CLK+_1), U8.39 (CLK+_1)
PC1HDMI-TMDSC-: J1.12 (TMDSCLOCK-), U5.38 (CLK-_1), U6.38 (CLK-_1), U7.38 (CLK-_1), U8.38 (CLK-_1)
PC1HDMI-TMDSD0+: J1.7 (TMDSDATA0+), U5.42 (D0+_1), U6.42 (D0+_1), U7.42 (D0+_1), U8.42 (D0+_1)
PC1HDMI-TMDSD0-: J1.9 (TMDSDATA0-), U5.41 (D0-_1), U6.41 (D0-_1), U7.41 (D0-_1), U8.41 (D0-_1)
PC1HDMI-TMDSD2+: J1.1 (TMDSDATA2+), U5.48 (D2+_1), U6.48 (D2+_1), U7.48 (D2+_1), U8.48 (D2+_1)
PC1HDMI-TMDSD2-: J1.3 (TMDSDATA2-), U5.47 (D2-_1), U6.47 (D2-_1), U7.47 (D2-_1), U8.47 (D2-_1)
PC1USBC-CC1: U1.39 (8B1), U2.39 (8B1), U3.39 (8B1), U4.39 (8B1), U$1.5 (CC1/VCONN)
PC1USBC-CC2: U1.52 (2B1), U2.52 (2B1), U3.52 (2B1), U4.52 (2B1), U$1.B5 (CC2/VCONN)
PC1USBC-D+: U1.41 (7B1), U2.41 (7B1), U3.41 (7B1), U4.41 (7B1), U$1.6 (D+), U$1.B6 (D+)
PC1USBC-D-: U1.43 (6B1), U2.43 (6B1), U3.43 (6B1), U4.43 (6B1), U$1.7 (D-), U$1.B7 (D-)
PC1USBC-GND: U1.30 (12B1), U2.30 (12B1), U3.30 (12B1), U4.30 (12B1), U$1.1 (GND), U$1.12 (GND), U$1.B1 (GND), U$1.B12 (GND)
PC1USBC-SBU: U1.45 (5B1), U2.45 (5B1), U3.45 (5B1), U4.45 (5B1), U$1.8 (SBU), U$1.B8 (SBU)
PC1USBC-SHIELD: U1.54 (1B1), U2.54 (1B1), U3.54 (1B1), U4.54 (1B1), U$1.P$1 (SHIELD), U$1.P$2 (SHIELD), U$1.P$3 (SHIELD), U$1.P$4 (SHIELD), U$1.P$5 (SHIELD), U$1.P$6 (SHIELD), U$1.P$7 (SHIELD), U$1.P$8 (SHIELD), U$1.P$9 (SHIELD), U$1.P$10 (SHIELD), U$1.P$11 (SHIELD), U$1.P$12 (SHIELD), U$1.P$13 (SHIELD), U$1.P$14 (SHIELD), U$1.P$15 (SHIELD), U$1.P$16 (SHIELD), U$1.P$17 (SHIELD), U$1.P$18 (SHIELD), U$1.P$19 (SHIELD), U$1.P$20 (SHIELD), U$1.P$21 (SHIELD), U$1.P$22 (SHIELD), U$1.P$23 (SHIELD), U$1.P$24 (SHIELD), U$1.P$25 (SHIELD), U$1.P$26 (SHIELD), U$1.P$27 (SHIELD), U$1.P$28 (SHIELD)
PC1USBC-SSRX+: U1.50 (3B1), U2.50 (3B1), U3.50 (3B1), U4.50 (3B1), U$1.11 (SSRX+), U$1.B11 (SSRX+)
PC1USBC-SSRX-: U1.47 (4B1), U2.47 (4B1), U3.47 (4B1), U4.47 (4B1), U$1.10 (SSRX-), U$1.B10 (SSRX-)
PC1USBC-SSTX+: U1.32 (11B1), U2.32 (11B1), U3.32 (11B1), U4.32 (11B1), U$1.2 (SSTX+), U$1.B2 (SSTX+)
PC1USBC-SSTX-: U1.34 (10B1), U2.34 (10B1), U3.34 (10B1), U4.34 (10B1), U$1.3 (SSTX-), U$1.B3 (SSTX-)
PC1USBC-VBUS: U1.36 (9B1), U2.36 (9B1), U3.36 (9B1), U4.36 (9B1), U$1.4 (VBUS), U$1.9 (VBUS), U$1.B4 (VBUS), U$1.B9 (VBUS)
PC2D+: U9.8 (HSD2+), U10.8 (HSD2+), U11.8 (HSD2+), U12.8 (HSD2+), U13.8 (HSD2+), U14.8 (HSD2+), U15.8 (HSD2+), U16.8 (HSD2+), U17.8 (HSD2+), U18.8 (HSD2+), U19.8 (HSD2+), U20.8 (HSD2+)
PC2D-: U9.7 (HSD2-), U10.7 (HSD2-), U11.7 (HSD2-), U12.7 (HSD2-), U13.7 (HSD2-), U14.7 (HSD2-), U15.7 (HSD2-), U16.7 (HSD2-), U17.7 (HSD2-), U18.7 (HSD2-), U19.7 (HSD2-), U20.7 (HSD2-)
PC2HDMI-HOT: U5.50 (HPD2), U6.50 (HPD2), U7.50 (HPD2), U8.50 (HPD2)
PC2HDMI-SCL: U5.2 (SCL3), U6.2 (SCL3), U7.2 (SCL3), U8.2 (SCL3)
PC2HDMI-SDA: U5.51 (SDA2), U6.51 (SDA2), U7.51 (SDA2), U8.51 (SDA2)
PC2HDMI-TMDS1+: U5.60 (D1+_2), U6.60 (D1+_2), U7.60 (D1+_2), U8.60 (D1+_2)
PC2HDMI-TMDS1-: U5.59 (D1-_2), U6.59 (D1-_2), U7.59 (D1-_2), U8.59 (D1-_2)
PC2HDMI-TMDSC+: U5.54 (CLK+_2), U6.54 (CLK+_2), U7.54 (CLK+_2), U8.54 (CLK+_2)
PC2HDMI-TMDSC-: U5.53 (CLK-_2), U6.53 (CLK-_2), U7.53 (CLK-_2), U8.53 (CLK-_2)
PC2HDMI-TMDSD0+: U5.57 (D0+_2), U6.57 (D0+_2), U7.57 (D0+_2), U8.57 (D0+_2)
PC2HDMI-TMDSD0-: U5.56 (D0-_2), U6.56 (D0-_2), U7.56 (D0-_2), U8.56 (D0-_2)
PC2HDMI-TMDSD2+: U5.63 (D2+_2), U6.63 (D2+_2), U7.63 (D2+_2), U8.63 (D2+_2)
PC2HDMI-TMDSD2-: U5.62 (D2-_2), U6.62 (D2-_2), U7.62 (D2-_2), U8.62 (D2-_2)
PC2USBC-CC1: U1.37 (8B2), U2.37 (8B2), U3.37 (8B2), U4.37 (8B2)
PC2USBC-CC2: U1.51 (2B2), U2.51 (2B2), U3.51 (2B2), U4.51 (2B2)
PC2USBC-D+: U1.40 (7B2), U2.40 (7B2), U3.40 (7B2), U4.40 (7B2)
PC2USBC-D-: U1.42 (6B2), U2.42 (6B2), U3.42 (6B2), U4.42 (6B2)
PC2USBC-GND: U1.29 (12B2), U2.29 (12B2), U3.29 (12B2), U4.29 (12B2)
PC2USBC-SBU: U1.44 (5B2), U2.44 (5B2), U3.44 (5B2), U4.44 (5B2)
PC2USBC-SHIELD: U1.53 (1B2), U2.53 (1B2), U3.53 (1B2), U4.53 (1B2)
PC2USBC-SSRX+: U1.48 (3B2), U2.48 (3B2), U3.48 (3B2), U4.48 (3B2)
PC2USBC-SSRX-: U1.46 (4B2), U2.46 (4B2), U3.46 (4B2), U4.46 (4B2)
PC2USBC-SSTX+: U1.31 (11B2), U2.31 (11B2), U3.31 (11B2), U4.31 (11B2)
PC2USBC-SSTX-: U1.33 (10B2), U2.33 (10B2), U3.33 (10B2), U4.33 (10B2)
PC2USBC-VBUS: U1.35 (9B2), U2.35 (9B2), U3.35 (9B2), U4.35 (9B2)
PC3D+: U9.10 (HSD3+), U10.10 (HSD3+), U11.10 (HSD3+), U12.10 (HSD3+), U13.10 (HSD3+), U14.10 (HSD3+), U15.10 (HSD3+), U16.10 (HSD3+), U17.10 (HSD3+), U18.10 (HSD3+), U19.10 (HSD3+), U20.10 (HSD3+)
PC3D-: U9.9 (HSD3-), U10.9 (HSD3-), U11.9 (HSD3-), U12.9 (HSD3-), U13.9 (HSD3-), U14.9 (HSD3-), U15.9 (HSD3-), U16.9 (HSD3-), U17.9 (HSD3-), U18.9 (HSD3-), U19.9 (HSD3-), U20.9 (HSD3-)
PC3HDMI-HOT: U5.64 (HPD3), U6.64 (HPD3), U7.64 (HPD3), U8.64 (HPD3)
PC3HDMI-SCL: U5.52 (SCL2), U6.52 (SCL2), U7.52 (SCL2), U8.52 (SCL2)
PC3HDMI-SDA: U5.1 (SDA3), U6.1 (SDA3), U7.1 (SDA3), U8.1 (SDA3)
PC3HDMI-TMDS1+: U5.11 (D1+_3), U6.11 (D1+_3), U7.11 (D1+_3), U8.11 (D1+_3)
PC3HDMI-TMDS1-: U5.10 (D1-_3), U6.10 (D1-_3), U7.10 (D1-_3), U8.10 (D1-_3)
PC3HDMI-TMDSC+: U5.5 (CLK+_3), U6.5 (CLK+_3), U7.5 (CLK+_3), U8.5 (CLK+_3)
PC3HDMI-TMDSC-: U5.4 (CLK-_3), U6.4 (CLK-_3), U7.4 (CLK-_3), U8.4 (CLK-_3)
PC3HDMI-TMDSD0+: U5.8 (D0+_3), U6.8 (D0+_3), U7.8 (D0+_3), U8.8 (D0+_3)
PC3HDMI-TMDSD0-: U5.7 (D0-_3), U6.7 (D0-_3), U7.7 (D0-_3), U8.7 (D0-_3)
PC3HDMI-TMDSD2+: U5.14 (D2+_3), U6.14 (D2+_3), U7.14 (D2+_3), U8.14 (D2+_3)
PC3HDMI-TMDSD2-: U5.13 (D2-_3), U6.13 (D2-_3), U7.13 (D2-_3), U8.13 (D2-_3)
PC3USBC-CC1: U1.20 (8B3), U2.20 (8B3), U3.20 (8B3), U4.20 (8B3)
PC3USBC-CC2: U1.5 (2B3), U2.5 (2B3), U3.5 (2B3), U4.5 (2B3)
PC3USBC-D+: U1.16 (7B3), U2.16 (7B3), U3.16 (7B3), U4.16 (7B3)
PC3USBC-D-: U1.14 (6B3), U2.14 (6B3), U3.14 (6B3), U4.14 (6B3)
PC3USBC-GND: U1.28 (12B3), U2.28 (12B3), U3.28 (12B3), U4.28 (12B3)
PC3USBC-SBU: U1.12 (5B3), U2.12 (5B3), U3.12 (5B3), U4.12 (5B3)
PC3USBC-SHIELD: U1.3 (1B3), U2.3 (1B3), U3.3 (1B3), U4.3 (1B3)
PC3USBC-SSRX+: U1.7 (3B3), U2.7 (3B3), U3.7 (3B3), U4.7 (3B3)
PC3USBC-SSRX-: U1.10 (4B3), U2.10 (4B3), U3.10 (4B3), U4.10 (4B3)
PC3USBC-SSTX+: U1.26 (11B3), U2.26 (11B3), U3.26 (11B3), U4.26 (11B3)
PC3USBC-SSTX-: U1.24 (10B3), U2.24 (10B3), U3.24 (10B3), U4.24 (10B3)
PC3USBC-VBUS: U1.22 (9B3), U2.22 (9B3), U3.22 (9B3), U4.22 (9B3)
SCL: J2.15 (SCL), J3.15 (SCL), J4.15 (SCL), J5.15 (SCL), U5.29 (SCL_SINK), U6.29 (SCL_SINK), U7.29 (SCL_SINK), U8.29 (SCL_SINK)
SDA: J2.16 (SDA), J3.16 (SDA), J4.16 (SDA), J5.16 (SDA), U5.30 (SDA_SINK), U6.30 (SDA_SINK), U7.30 (SDA_SINK), U8.30 (SDA_SINK)
USBGND: U9.3 (GND), U10.3 (GND), U11.3 (GND), U12.3 (GND), U13.3 (GND), U14.3 (GND), U15.3 (GND), U16.3 (GND), U17.3 (GND), U18.3 (GND), U19.3 (GND), U20.3 (GND), X1.GND, X2.GND, X3.GND, X4.GND, X5.GND, X6.GND, X7.GND, X8.GND, X9.GND, X10.GND, X11.GND, X12.GND, X13.GND
USBVCC: S5.3, S6.3, S7.3, S8.3, S9.3, S10.3, S11.3, S12.3, S13.3, S14.3, S15.3, S16.3, U9.12 (VCC), U10.12 (VCC), U11.12 (VCC), U12.12 (VCC), U13.12 (VCC), U14.12 (VCC), U15.12 (VCC), U16.12 (VCC), U17.12 (VCC), U18.12 (VCC), U19.12 (VCC), U20.12 (VCC), X1.VBUS, X2.VBUS, X3.VBUS, X4.VBUS, X5.VBUS, X6.VBUS, X7.VBUS, X8.VBUS, X9.VBUS, X10.VBUS, X11.VBUS, X12.VBUS, X13.VBUS
VBUS: U1.21 (9A), U2.21 (9A), U3.21 (9A), U4.21 (9A), U$2.4 (VBUS), U$2.9 (VBUS), U$2.B4 (VBUS), U$2.B9 (VBUS), U$3.4 (VBUS), U$3.9 (VBUS), U$3.B4 (VBUS), U$3.B9 (VBUS), U$4.4 (VBUS), U$4.9 (VBUS), U$4.B4 (VBUS), U$4.B9 (VBUS), U$5.4 (VBUS), U$5.9 (VBUS), U$5.B4 (VBUS), U$5.B9 (VBUS)
VDD: U21.19 (VDD), U22.19 (VDD)
VDD_2: U21.7 (VDD_2), U22.7 (VDD_2)
VDD_3: U21.9 (VDD_3), U22.9 (VDD_3)
VDD_4: U21.15 (VDD_4), U22.15 (VDD_4)

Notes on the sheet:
PC1
USB Type C IN/OUT
HDMI
USB A
ETHERNET

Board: 2 copper layers, 89 parts (0 on the bottom side), 240 nets, no tracks yet.
